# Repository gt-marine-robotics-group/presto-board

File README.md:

# PRESTO Board

The PRESTO (Peripheral, Radio, and E-Stop) Mainboard project is intended to provide interfaces for standard servo-based peripherals and the emergency stop. Functions that PRESTO provides include direct servo commands, receiving radio control signals, triggering the emergency stop, sensing the emergency stop, and outputing status to a light tower.

## Board Variants

### Presto
Presto is the full functionality variant, designed with as many servo interfaces as possible. This version is intended to serve as an interface for computers with thrusters and peripherals.

### Presto Jr.
Presto Jr. is a reduced functionality variant, with fewer servo interfaces. This version is intended to complement systems with existing frontseat boards controlling thrusters which need to be retrofitted with E-Stop and additional peripherals. 

## Firmware
Firmware can be found [here](https://github.com/gt-marine-robotics-group/firmware-base).

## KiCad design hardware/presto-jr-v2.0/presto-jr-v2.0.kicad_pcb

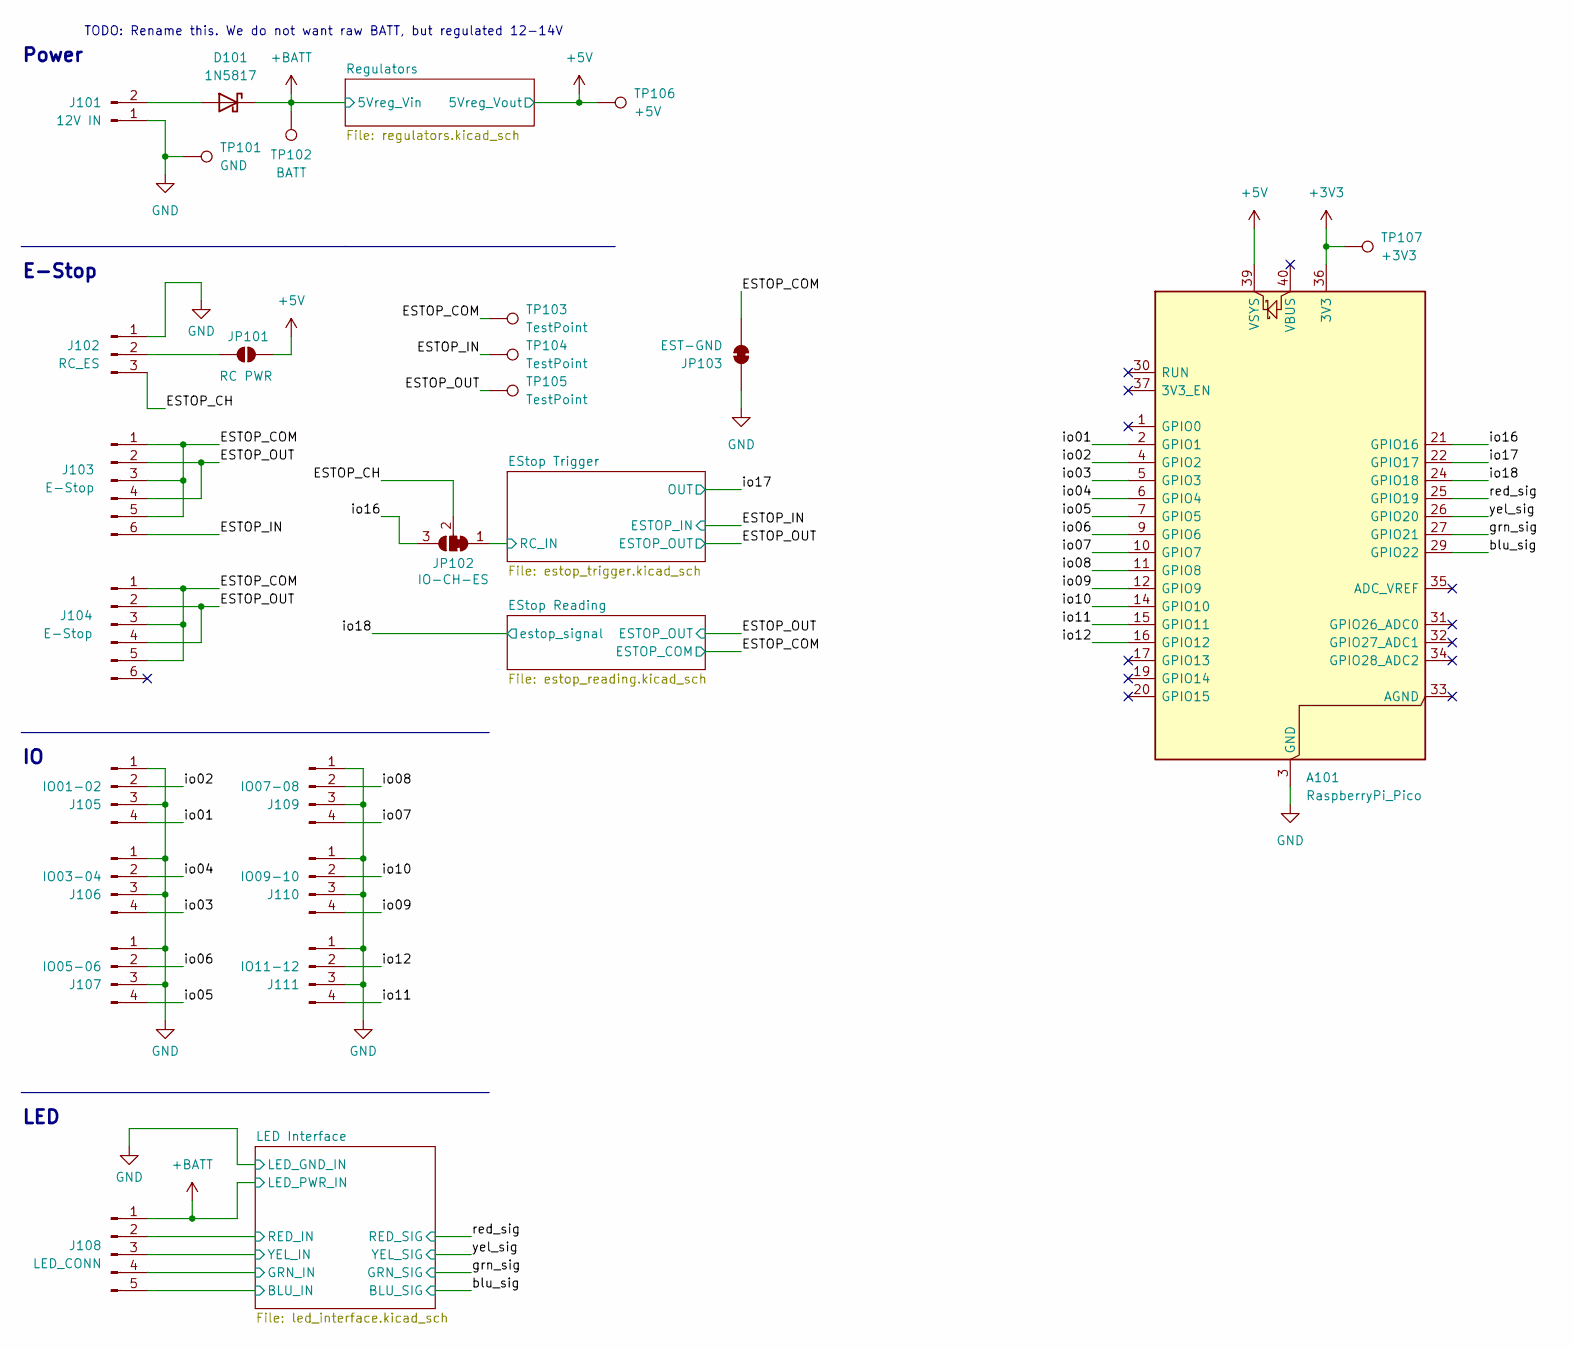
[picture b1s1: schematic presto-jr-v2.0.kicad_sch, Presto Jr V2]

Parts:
A101: RaspberryPi_Pico; RaspberryPi_Pico_SMD_HandSolder
D101: 1N5817; D_DO-41_SOD81_P10.16mm_Horizontal
J101: 12V IN; AMASS_XT30PW-M_1x02_P2.50mm_Horizontal
J102: RC_ES; JST_XH_S3B-XH-SM4-TB_1x03-1MP_P2.50mm_Horizontal
J103, J104: E-Stop; JST_XH_S6B-XH-SM4-TB_1x06-1MP_P2.50mm_Horizontal
J105: IO01-02; JST_XH_S4B-XH-SM4-TB_1x04-1MP_P2.50mm_Horizontal
J106: IO03-04; JST_XH_S4B-XH-SM4-TB_1x04-1MP_P2.50mm_Horizontal
J107: IO05-06; JST_XH_S4B-XH-SM4-TB_1x04-1MP_P2.50mm_Horizontal
J108: LED_CONN; JST_XH_S5B-XH-SM4-TB_1x05-1MP_P2.50mm_Horizontal
J109: IO07-08; JST_XH_S4B-XH-SM4-TB_1x04-1MP_P2.50mm_Horizontal
J110: IO09-10; JST_XH_B4B-XH-A_1x04_P2.50mm_Vertical
J111: IO11-12; JST_XH_B4B-XH-A_1x04_P2.50mm_Vertical
JP101: RC PWR; SolderJumper-2_P1.3mm_Open_RoundedPad1.0x1.5mm
JP102: IO-CH-ES; SolderJumper-3_P1.3mm_Bridged2Bar12_RoundedPad1.0x1.5mm
JP103: EST-GND; SolderJumper-2_P1.3mm_Bridged_RoundedPad1.0x1.5mm
TP101: GND; TestPoint_THTPad_2.5x2.5mm_Drill1.2mm
TP102: BATT; TestPoint_THTPad_2.5x2.5mm_Drill1.2mm
TP103, TP104, TP105: TestPoint; TestPoint_THTPad_2.5x2.5mm_Drill1.2mm
TP106: +5V; TestPoint_THTPad_2.5x2.5mm_Drill1.2mm
TP107: +3V3; TestPoint_THTPad_2.5x2.5mm_Drill1.2mm

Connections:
+3V3: A101.36 (3V3), TP107.1 (1_1); also elsewhere on the board
+5V: A101.39 (VSYS), JP101.1 (A), TP106.1 (1_1); also elsewhere on the board
+BATT: D101.1 (K), J108.1, TP102.1 (1_1); also elsewhere on the board
/ESTOP_CH: J102.3, JP102.2 (C)
/ESTOP_COM: J103.1, J103.3, J103.5, J104.1, J104.3, J104.5, JP103.1 (A), TP103.1 (1_1); also elsewhere on the board
/ESTOP_IN: J103.6, TP104.1 (1_1); also elsewhere on the board
/ESTOP_OUT: J103.2, J103.4, J104.2, J104.4, TP105.1 (1_1); also elsewhere on the board
/EStop Trigger/RC_IN: JP102.1 (A); also elsewhere on the board
/LED Interface/BLU_IN: J108.5; also elsewhere on the board
/LED Interface/GRN_IN: J108.4; also elsewhere on the board
/LED Interface/RED_IN: J108.2; also elsewhere on the board
/LED Interface/YEL_IN: J108.3; also elsewhere on the board
/blu_sig: A101.29 (GPIO22); also elsewhere on the board
/grn_sig: A101.27 (GPIO21); also elsewhere on the board
/io01: A101.2 (GPIO1), J105.4
/io02: A101.4 (GPIO2), J105.2
/io03: A101.5 (GPIO3), J106.4
/io04: A101.6 (GPIO4), J106.2
/io05: A101.7 (GPIO5), J107.4
/io06: A101.9 (GPIO6), J107.2
/io07: A101.10 (GPIO7), J109.4
/io08: A101.11 (GPIO8), J109.2
/io09: A101.12 (GPIO9), J110.4
/io10: A101.14 (GPIO10), J110.2
/io11: A101.15 (GPIO11), J111.4
/io12: A101.16 (GPIO12), J111.2
/io16: A101.21 (GPIO16), JP102.3 (B)
/io17: A101.22 (GPIO17); also elsewhere on the board
/io18: A101.24 (GPIO18); also elsewhere on the board
/red_sig: A101.25 (GPIO19); also elsewhere on the board
/yel_sig: A101.26 (GPIO20); also elsewhere on the board
unnamed: D101.2 (A), J101.2
unnamed: J102.2, JP101.2 (B)

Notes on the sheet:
E-Stop
LED
Power
TODO: Rename this. We do not want raw BATT, but regulated 12-14V

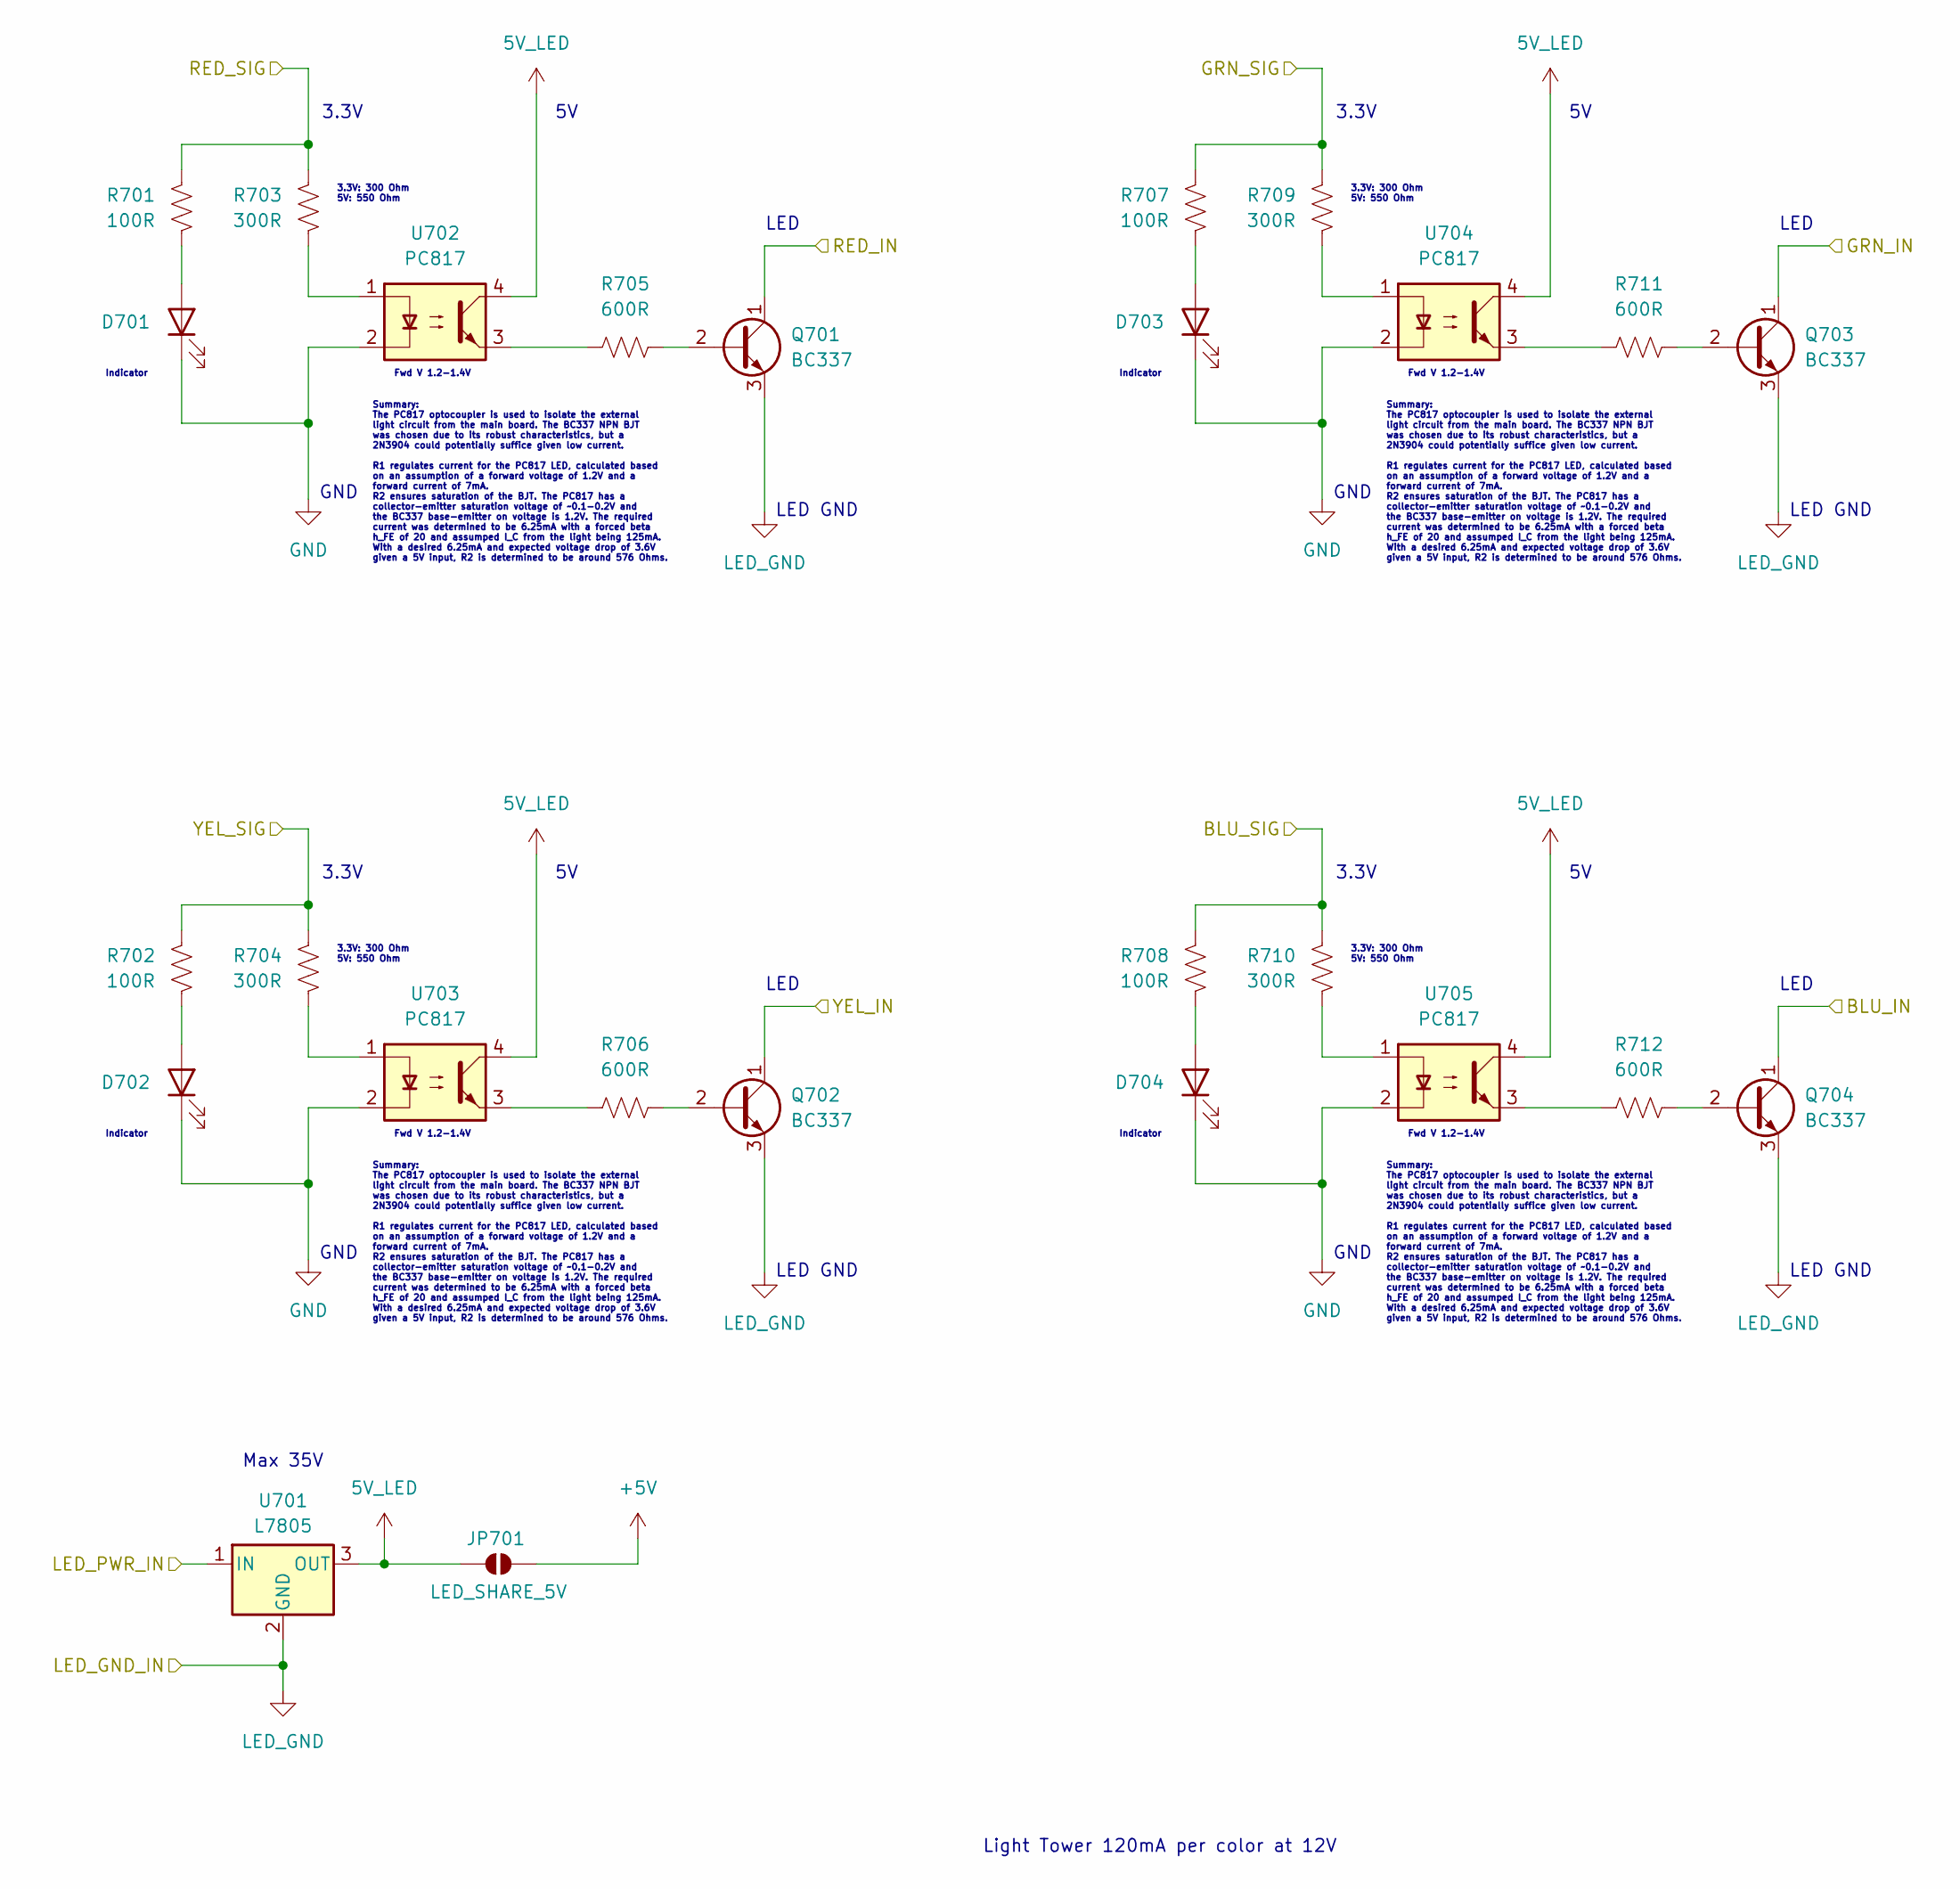
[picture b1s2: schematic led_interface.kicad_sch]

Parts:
D701, D702, D703, D704: LED; LED_1206_3216Metric_Pad1.42x1.75mm_HandSolder
JP701: LED_SHARE_5V; SolderJumper-2_P1.3mm_Open_RoundedPad1.0x1.5mm
Q701, Q702, Q703, Q704: BC337; TO-92_Inline
R701, R702, R707, R708: 100R; R_1206_3216Metric_Pad1.30x1.75mm_HandSolder
R703, R704, R709, R710: 300R; R_1206_3216Metric_Pad1.30x1.75mm_HandSolder
R705, R706, R711, R712: 600R; R_1206_3216Metric_Pad1.30x1.75mm_HandSolder
U701: L7805; TO-220-3_Horizontal_TabDown
U702, U703, U704, U705: PC817; DIP-4_W7.62mm

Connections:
5V_LED: JP701.1 (A), U701.3 (OUT), U702.4, U703.4, U704.4, U705.4
+5V: JP701.2 (B); also elsewhere on the board
+BATT: U701.1 (IN); also elsewhere on the board
/LED Interface/BLU_IN: Q704.1 (C); also elsewhere on the board
/LED Interface/GRN_IN: Q703.1 (C); also elsewhere on the board
/LED Interface/RED_IN: Q701.1 (C); also elsewhere on the board
/LED Interface/YEL_IN: Q702.1 (C); also elsewhere on the board
/blu_sig: R708.1, R710.1; also elsewhere on the board
/grn_sig: R707.1, R709.1; also elsewhere on the board
/red_sig: R701.1, R703.1; also elsewhere on the board
/yel_sig: R702.1, R704.1; also elsewhere on the board
unnamed: D701.2 (A), R701.2
unnamed: D702.2 (A), R702.2
unnamed: D703.2 (A), R707.2
unnamed: D704.2 (A), R708.2
unnamed: Q701.2 (B), R705.2
unnamed: Q702.2 (B), R706.2
unnamed: Q703.2 (B), R711.2
unnamed: Q704.2 (B), R712.2
unnamed: R703.2, U702.1
unnamed: R704.2, U703.1
unnamed: R705.1, U702.3
unnamed: R706.1, U703.3
unnamed: R709.2, U704.1
unnamed: R710.2, U705.1
unnamed: R711.1, U704.3
unnamed: R712.1, U705.3

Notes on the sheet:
3.3V: 300 Ohm 5V: 550 Ohm
Summary: The PC817 optocoupler is used to isolate the external light circuit from the main board. The BC337 NPN BJT was chosen due to its robust characteristics, but a 2N3904 could potentially suffice given low current. R1 regulates current for the PC817 LED, calculated based on an assumption of a 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
LED GND
Indicator
Light Tower 120mA per color at 12V
LED
3.3V
GND
Fwd V 1.2-1.4V
Max 35V

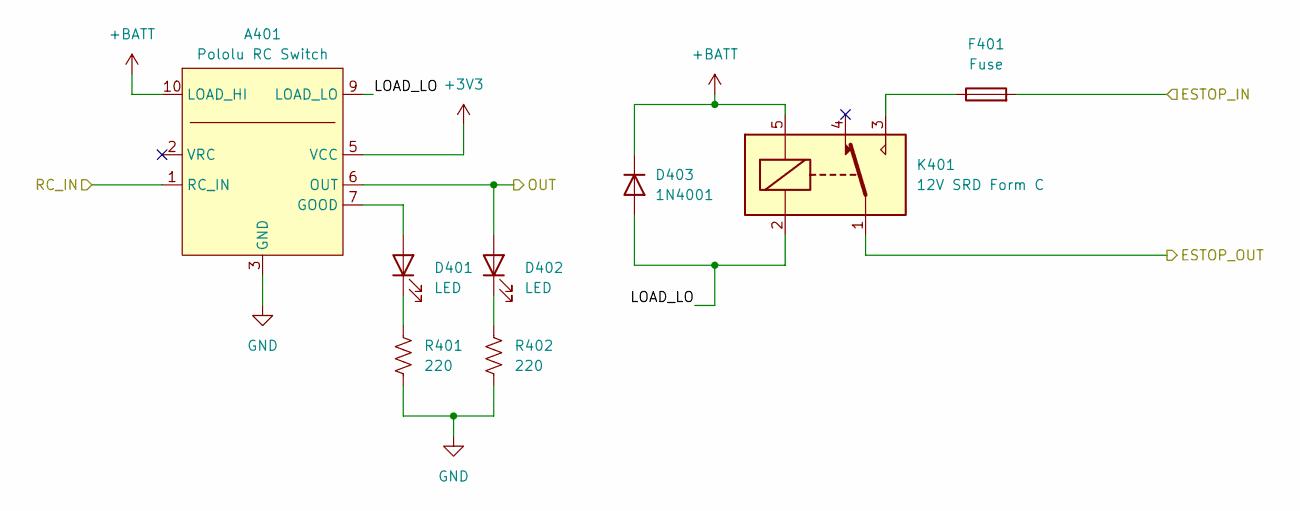
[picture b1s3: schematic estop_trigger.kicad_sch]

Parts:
A401: Pololu RC Switch; Pololu_2802_RCSw
D401, D402: LED; LED_1206_3216Metric_Pad1.42x1.75mm_HandSolder
D403: 1N4001; D_DO-41_SOD81_P10.16mm_Horizontal
F401: Fuse; Fuseholder_Blade_Mini_Keystone_3568
K401: 12V SRD Form C; Relay_SPDT_SANYOU_SRD_Series_Form_C
R401, R402: 220; R_1206_3216Metric_Pad1.30x1.75mm_HandSolder

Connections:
+3V3: A401.5 (VCC); also elsewhere on the board
+BATT: A401.10 (LOAD_HI), A401.11 (LOAD_HI), D403.1 (K), K401.5; also elsewhere on the board
/ESTOP_IN: F401.2; also elsewhere on the board
/ESTOP_OUT: K401.1; also elsewhere on the board
/EStop Trigger/LOAD_LO: A401.9 (LOAD_LO), D403.2 (A), K401.2
/EStop Trigger/RC_IN: A401.1 (RC_IN); also elsewhere on the board
/io17: A401.6 (OUT), D402.2 (A); also elsewhere on the board
unnamed: A401.7 (GOOD), D401.2 (A)
unnamed: D401.1 (K), R401.1
unnamed: D402.1 (K), R402.1
unnamed: F401.1, K401.3

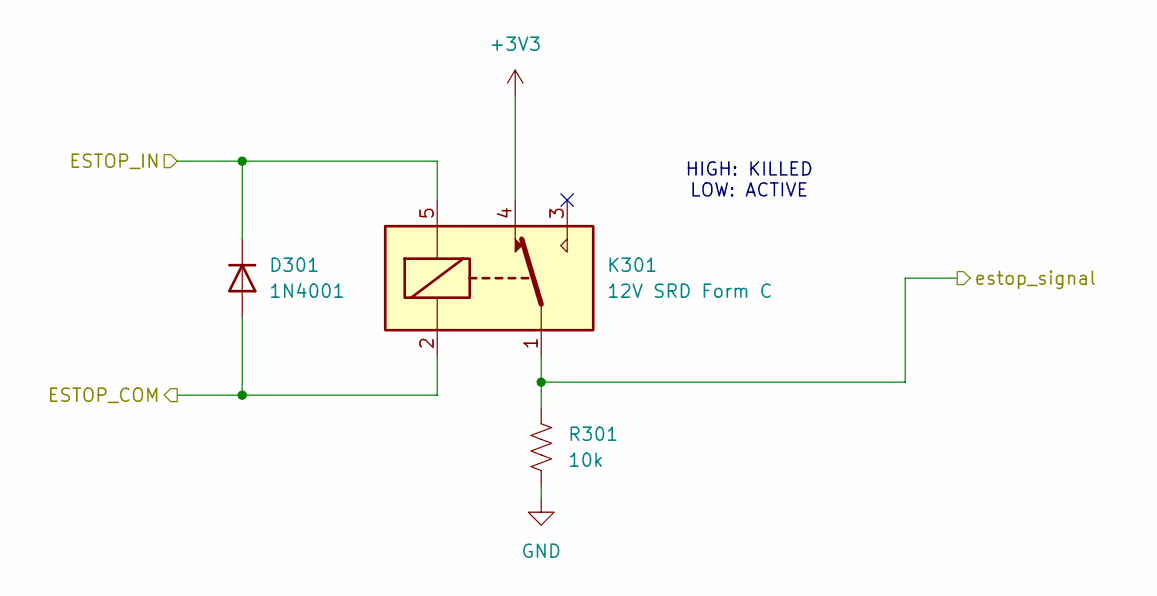
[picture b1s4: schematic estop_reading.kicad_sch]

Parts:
D301: 1N4001; D_DO-41_SOD81_P10.16mm_Horizontal
K301: 12V SRD Form C; Relay_SPDT_SANYOU_SRD_Series_Form_C
R301: 10k; R_Axial_DIN0207_L6.3mm_D2.5mm_P10.16mm_Horizontal

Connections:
+3V3: K301.4; also elsewhere on the board
/ESTOP_COM: D301.2 (A), K301.2; also elsewhere on the board
/EStop Reading/ESTOP_IN: D301.1 (K), K301.5
/io18: K301.1, R301.1; also elsewhere on the board

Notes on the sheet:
HIGH: KILLED LOW: ACTIVE

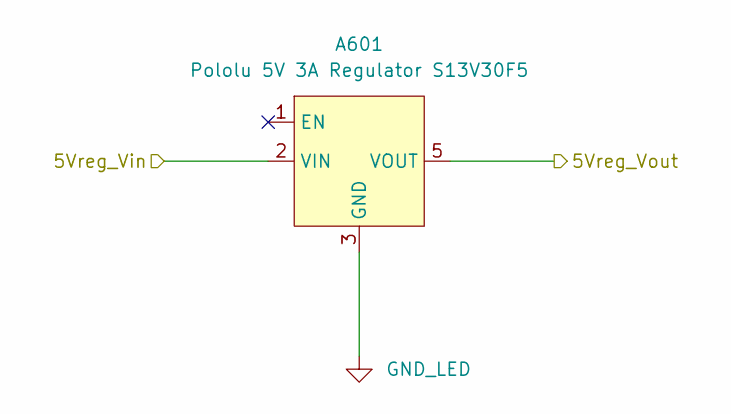
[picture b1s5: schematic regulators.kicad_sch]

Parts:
A601: Pololu 5V 3A Regulator S13V30F5; Pololu_S13V30F5

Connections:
+5V: A601.5 (VOUT); also elsewhere on the board
+BATT: A601.2 (VIN); also elsewhere on the board

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
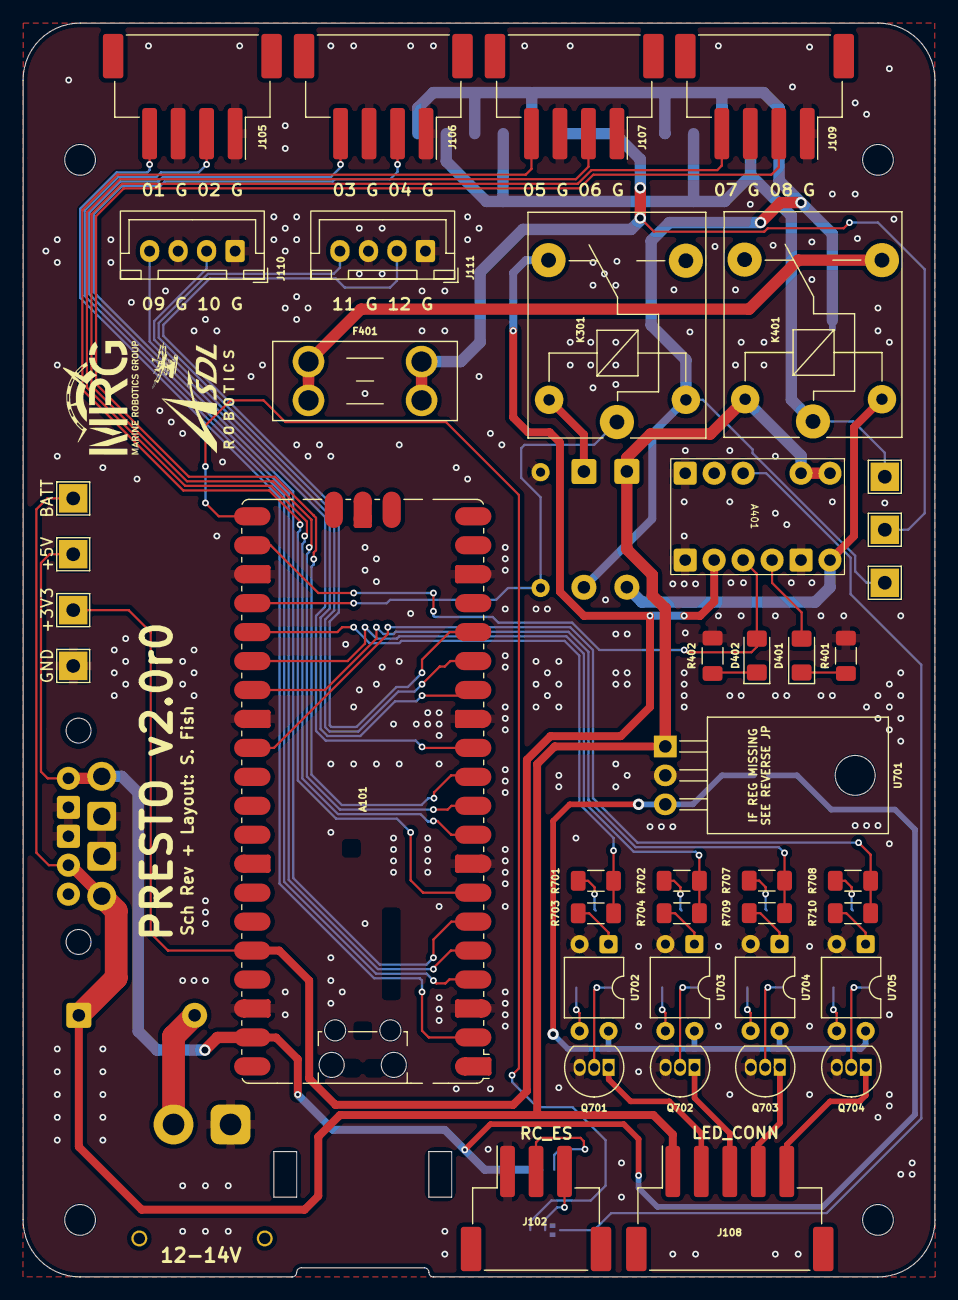
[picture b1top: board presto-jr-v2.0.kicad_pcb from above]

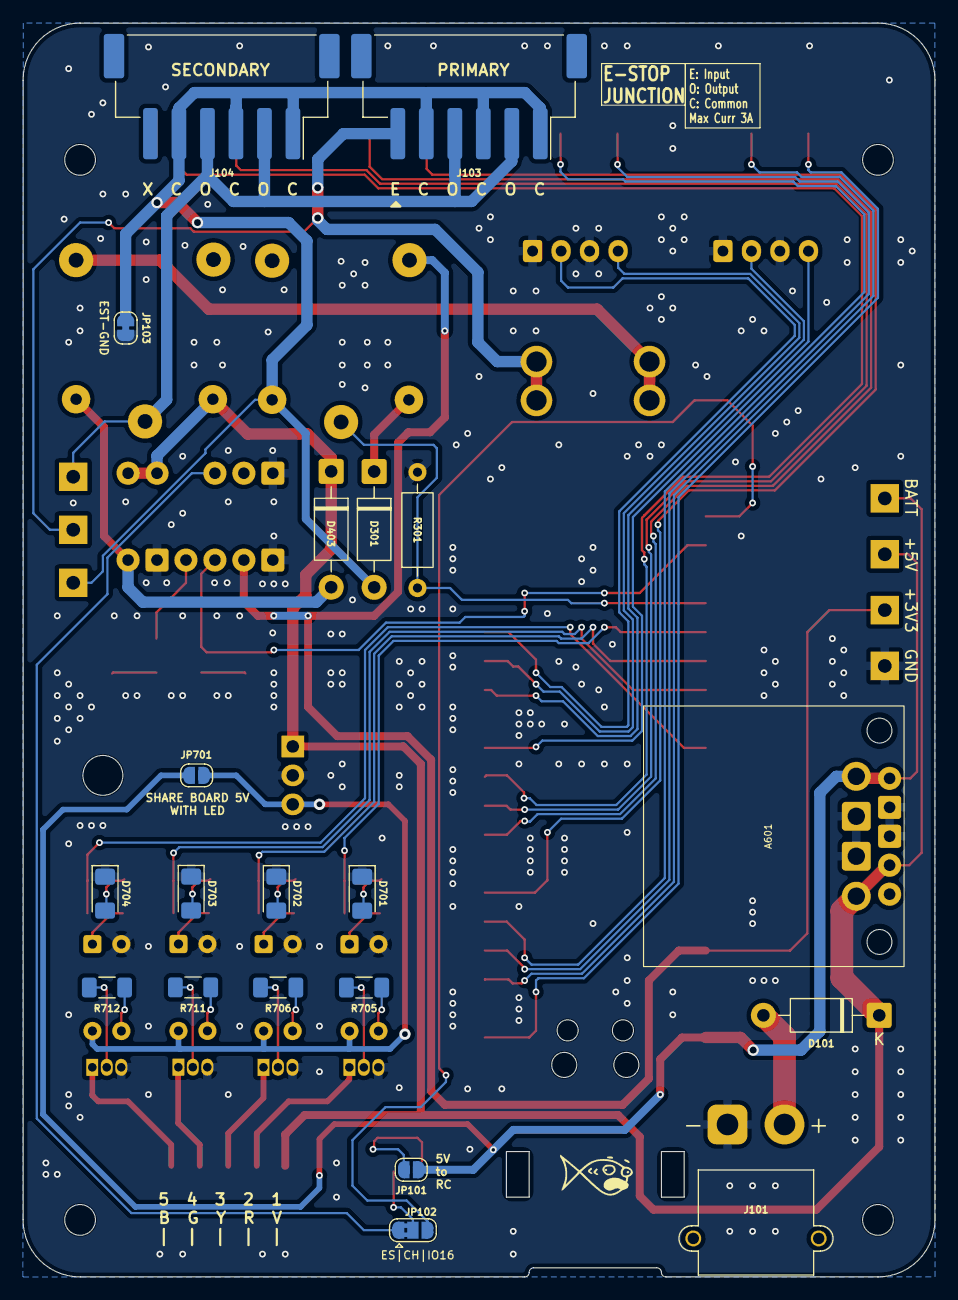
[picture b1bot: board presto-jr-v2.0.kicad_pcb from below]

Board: 2 copper layers, 80.0 x 110.0 mm, 61 parts (20 on the bottom side), 57 nets.

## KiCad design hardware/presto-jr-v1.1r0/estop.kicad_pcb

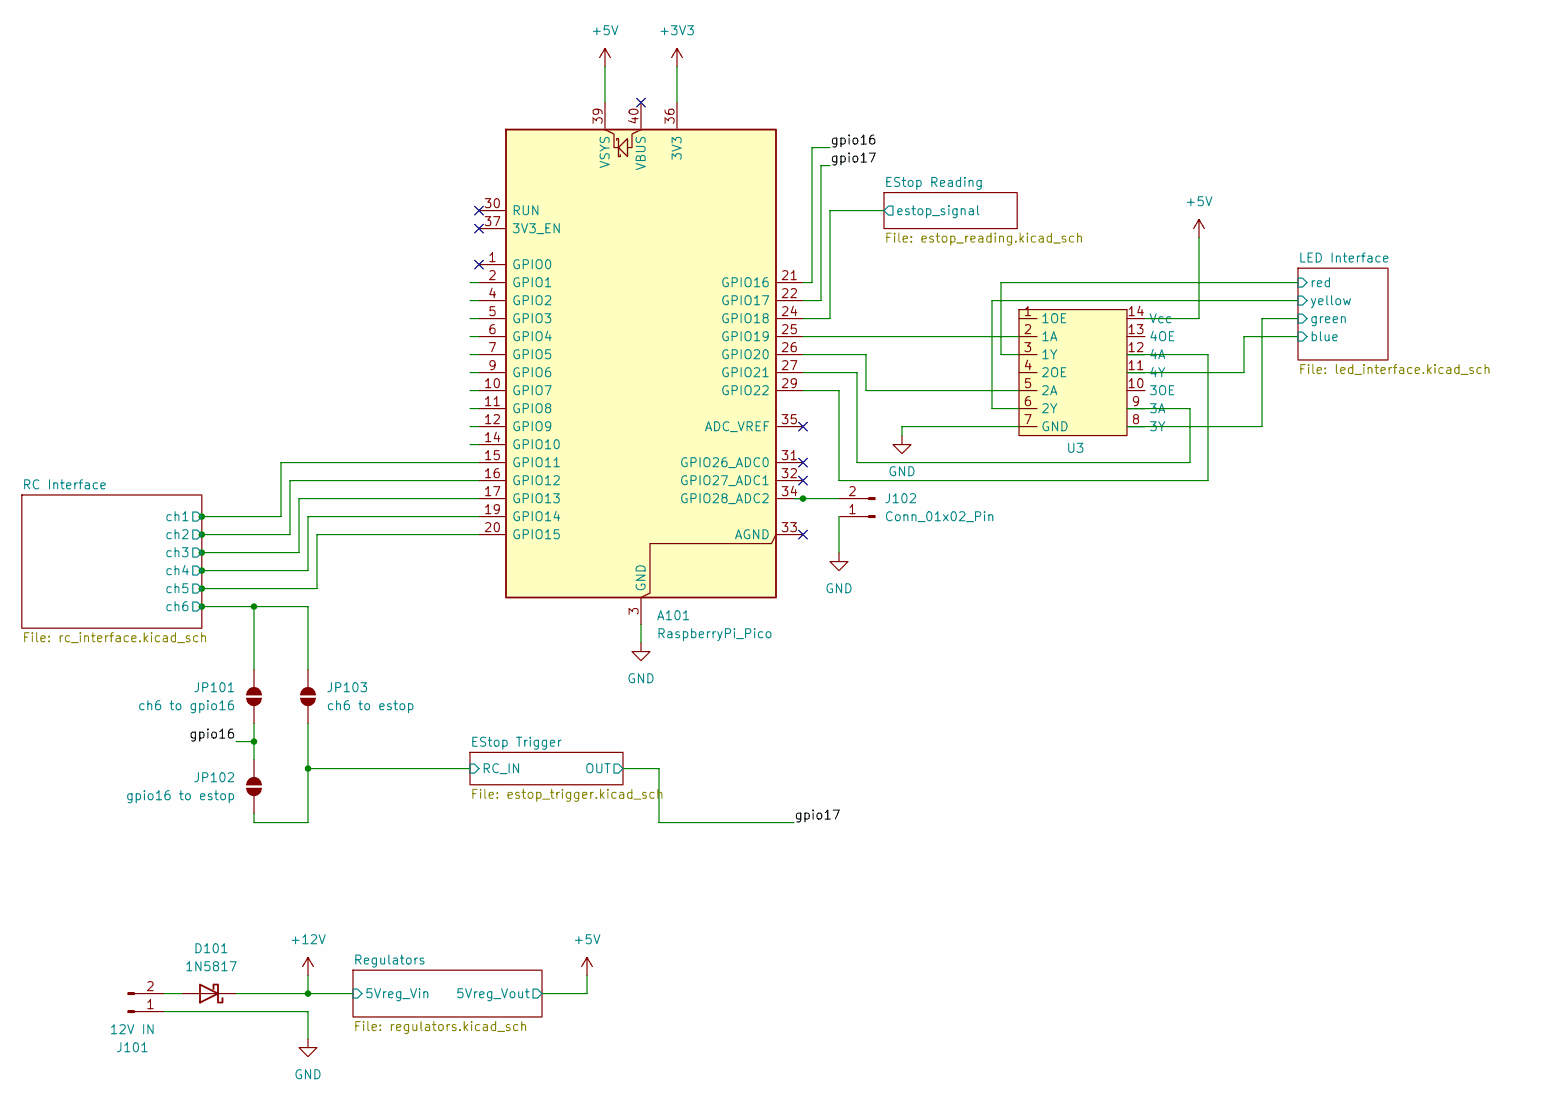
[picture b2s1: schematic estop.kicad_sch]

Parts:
A101: RaspberryPi_Pico; RaspberryPi_Pico_Common_Unspecified
D101: 1N5817; D_DO-41_SOD81_P10.16mm_Horizontal
J101: 12V IN; AMASS_XT30PW-M_1x02_P2.50mm_Horizontal
J102: Conn_01x02_Pin; JST_XH_B2B-XH-A_1x02_P2.50mm_Vertical
JP101: ch6 to gpio16; SolderJumper-2_P1.3mm_Open_RoundedPad1.0x1.5mm
JP102: gpio16 to estop; SolderJumper-2_P1.3mm_Open_RoundedPad1.0x1.5mm
JP103: ch6 to estop; SolderJumper-2_P1.3mm_Open_RoundedPad1.0x1.5mm
U3: DIP-14_W7.62mm_Socket_LongPads

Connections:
+3V3: A101.36 (3V3); also elsewhere on the board
+5V: A101.39 (VSYS); also elsewhere on the board
+12V: D101.1 (K); also elsewhere on the board
/EStop Reading/estop_signal: A101.24 (GPIO18); also elsewhere on the board
/EStop Trigger/RC_IN: JP102.2 (B), JP103.2 (B); also elsewhere on the board
/LED Interface/blue: U3.11 (4Y); also elsewhere on the board
/LED Interface/green: U3.8 (3Y); also elsewhere on the board
/LED Interface/red: U3.3 (1Y); also elsewhere on the board
/LED Interface/yellow: U3.6 (2Y); also elsewhere on the board
/RC Interface/ch1: A101.15 (GPIO11); also elsewhere on the board
/RC Interface/ch2: A101.16 (GPIO12); also elsewhere on the board
/RC Interface/ch3: A101.17 (GPIO13); also elsewhere on the board
/RC Interface/ch4: A101.19 (GPIO14); also elsewhere on the board
/RC Interface/ch5: A101.20 (GPIO15); also elsewhere on the board
/RC Interface/ch6: JP101.1 (A), JP103.1 (A); also elsewhere on the board
/gpio16: A101.21 (GPIO16), JP101.2 (B), JP102.1 (A)
/gpio17: A101.22 (GPIO17); also elsewhere on the board
GND: A101.3 (GND), A101.8 (GND), A101.13 (GND), A101.18 (GND), A101.23 (GND), A101.28 (GND), A101.38 (GND), J101.1, J102.1, U3.7 (GND); also elsewhere on the board
unnamed: A101.25 (GPIO19), U3.2 (1A)
unnamed: A101.26 (GPIO20), U3.5 (2A)
unnamed: A101.27 (GPIO21), U3.9 (3A)
unnamed: A101.29 (GPIO22), U3.12 (4A)
unnamed: A101.34 (GPIO28_ADC2), J102.2
unnamed: D101.2 (A), J101.2

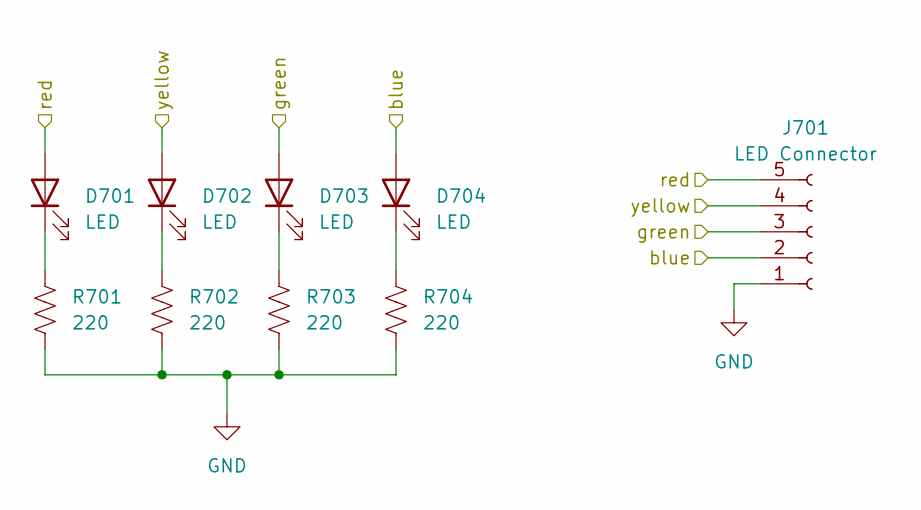
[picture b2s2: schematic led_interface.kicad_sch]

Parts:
D701, D702, D703, D704: LED; LED_1206_3216Metric_Pad1.42x1.75mm_HandSolder
J701: LED Connector; JST_XH_B5B-XH-A_1x05_P2.50mm_Vertical
R701, R702, R703, R704: 220; R_1206_3216Metric_Pad1.30x1.75mm_HandSolder

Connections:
/LED Interface/blue: D704.2 (A), J701.2; also elsewhere on the board
/LED Interface/green: D703.2 (A), J701.3; also elsewhere on the board
/LED Interface/red: D701.2 (A), J701.5; also elsewhere on the board
/LED Interface/yellow: D702.2 (A), J701.4; also elsewhere on the board
GND: J701.1, R701.2, R702.2, R703.2, R704.2; also elsewhere on the board
unnamed: D701.1 (K), R701.1
unnamed: D702.1 (K), R702.1
unnamed: D703.1 (K), R703.1
unnamed: D704.1 (K), R704.1

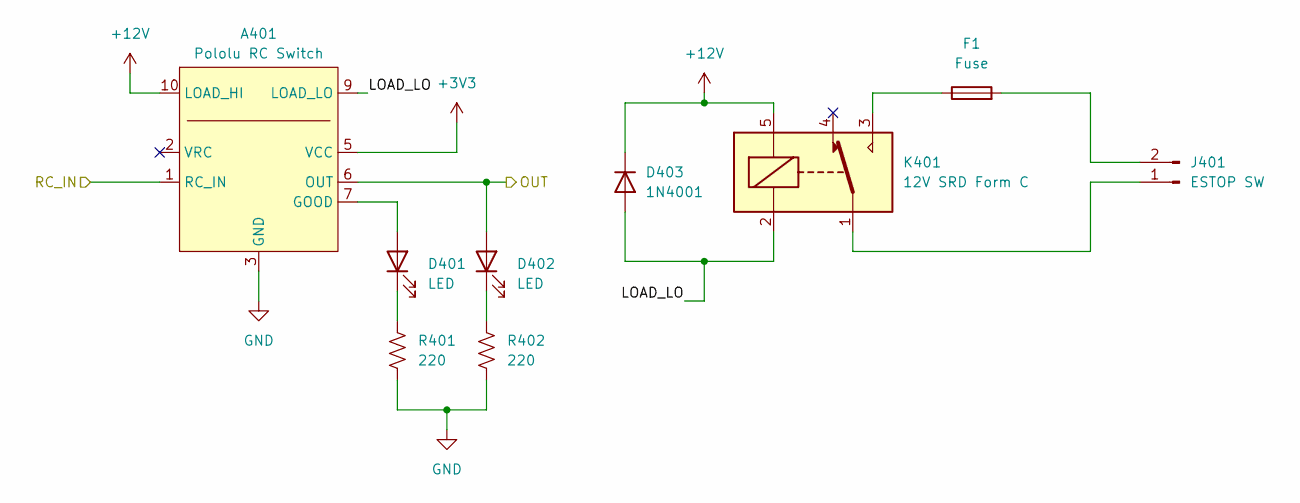
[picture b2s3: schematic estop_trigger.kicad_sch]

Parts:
A401: Pololu RC Switch; Pololu_2802_RCSw
D401, D402: LED; LED_1206_3216Metric_Pad1.42x1.75mm_HandSolder
D403: 1N4001; D_DO-41_SOD81_P10.16mm_Horizontal
F1: Fuse; Fuseholder_Blade_Mini_Keystone_3568
J401: ESTOP SW; AMASS_XT30PW-M_1x02_P2.50mm_Horizontal
K401: 12V SRD Form C; Relay_SPDT_SANYOU_SRD_Series_Form_C
R401, R402: 220; R_1206_3216Metric_Pad1.30x1.75mm_HandSolder

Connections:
+3V3: A401.5 (VCC); also elsewhere on the board
+12V: A401.10 (LOAD_HI), A401.11 (LOAD_HI), D403.1 (K), K401.5; also elsewhere on the board
/EStop Trigger/LOAD_LO: A401.9 (LOAD_LO), D403.2 (A), K401.2
/EStop Trigger/RC_IN: A401.1 (RC_IN); also elsewhere on the board
/gpio17: A401.6 (OUT), D402.2 (A); also elsewhere on the board
GND: A401.3 (GND), A401.4 (GND), A401.8 (GND), R401.2, R402.2; also elsewhere on the board
unnamed: A401.7 (GOOD), D401.2 (A)
unnamed: D401.1 (K), R401.1
unnamed: D402.1 (K), R402.1
unnamed: F1.1, K401.3
unnamed: J401.1, K401.1
unnamed: F1.2, J401.2

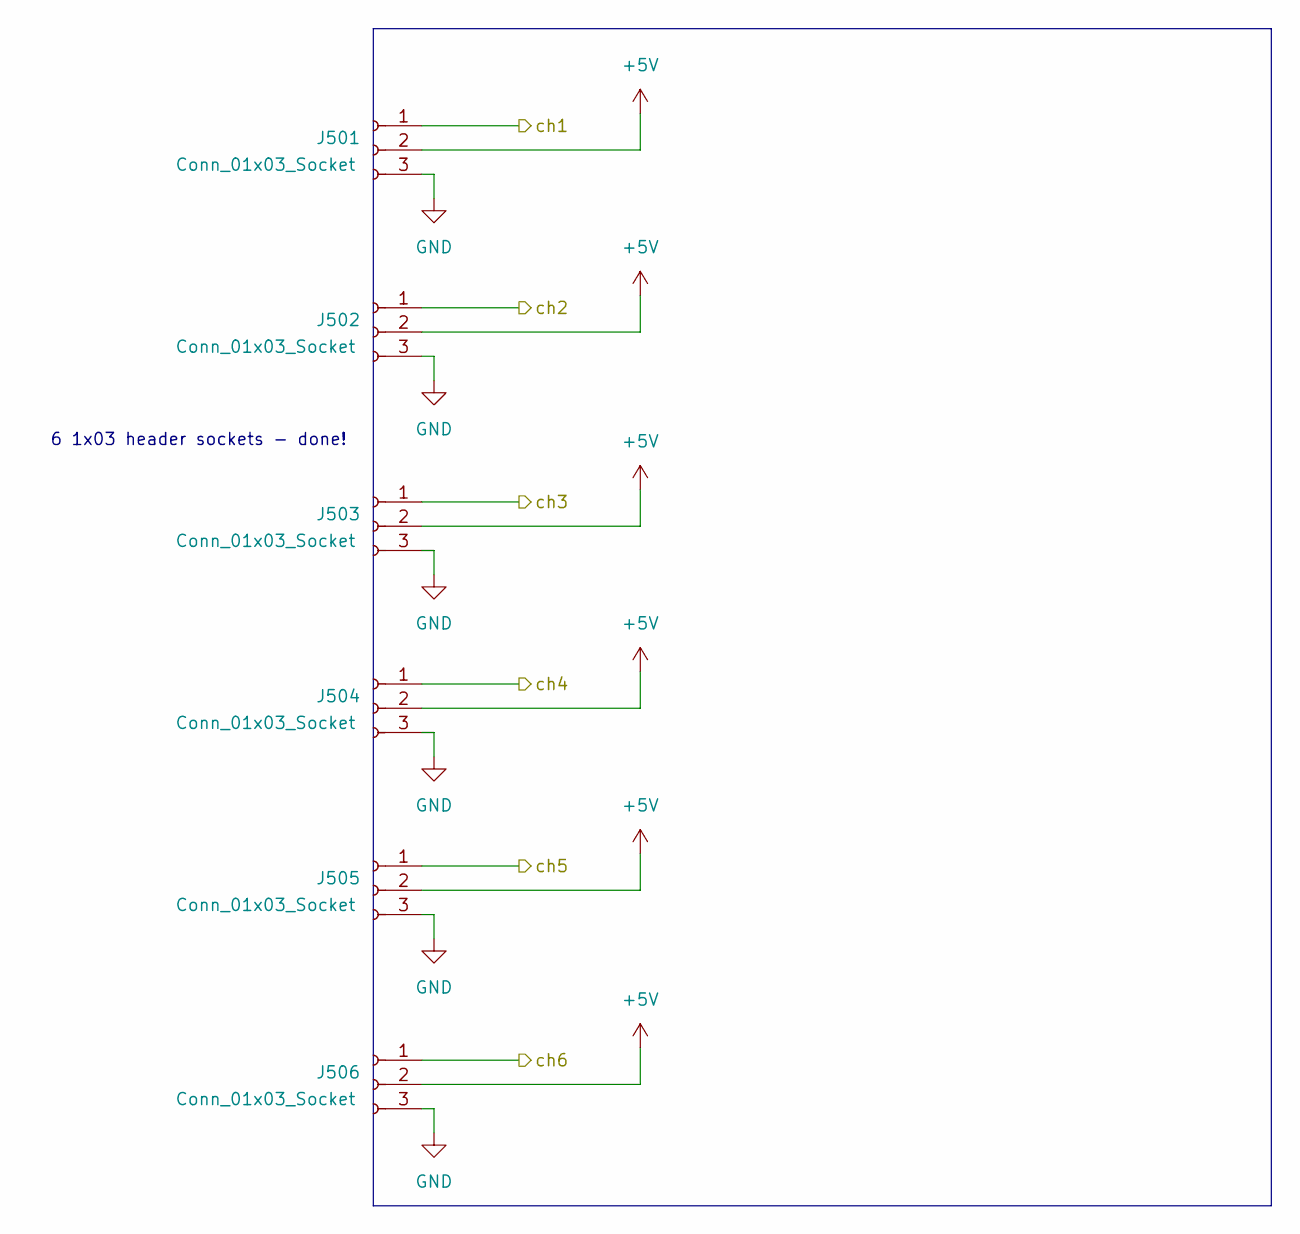
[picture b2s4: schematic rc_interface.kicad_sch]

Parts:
J501, J502, J503, J504, J505, J506: Conn_01x03_Socket; PinSocket_1x03_P2.54mm_Vertical

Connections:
+5V: J501.2, J502.2, J503.2, J504.2, J505.2, J506.2; also elsewhere on the board
/RC Interface/ch1: J501.1; also elsewhere on the board
/RC Interface/ch2: J502.1; also elsewhere on the board
/RC Interface/ch3: J503.1; also elsewhere on the board
/RC Interface/ch4: J504.1; also elsewhere on the board
/RC Interface/ch5: J505.1; also elsewhere on the board
/RC Interface/ch6: J506.1; also elsewhere on the board
GND: J501.3, J502.3, J503.3, J504.3, J505.3, J506.3; also elsewhere on the board

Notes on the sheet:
6 1x03 header sockets - done!
